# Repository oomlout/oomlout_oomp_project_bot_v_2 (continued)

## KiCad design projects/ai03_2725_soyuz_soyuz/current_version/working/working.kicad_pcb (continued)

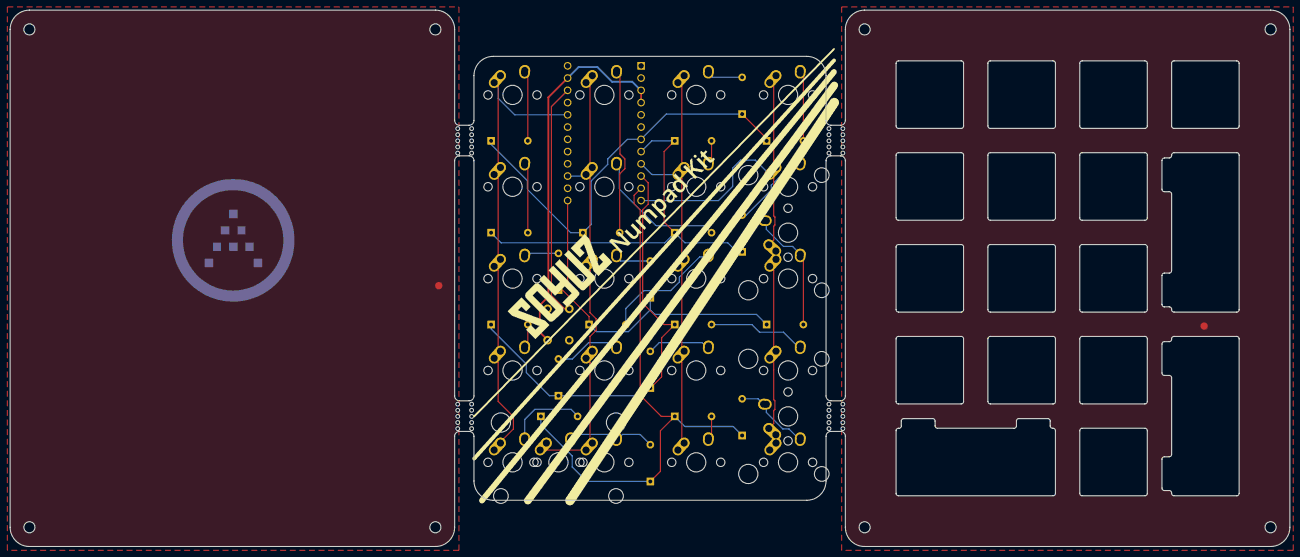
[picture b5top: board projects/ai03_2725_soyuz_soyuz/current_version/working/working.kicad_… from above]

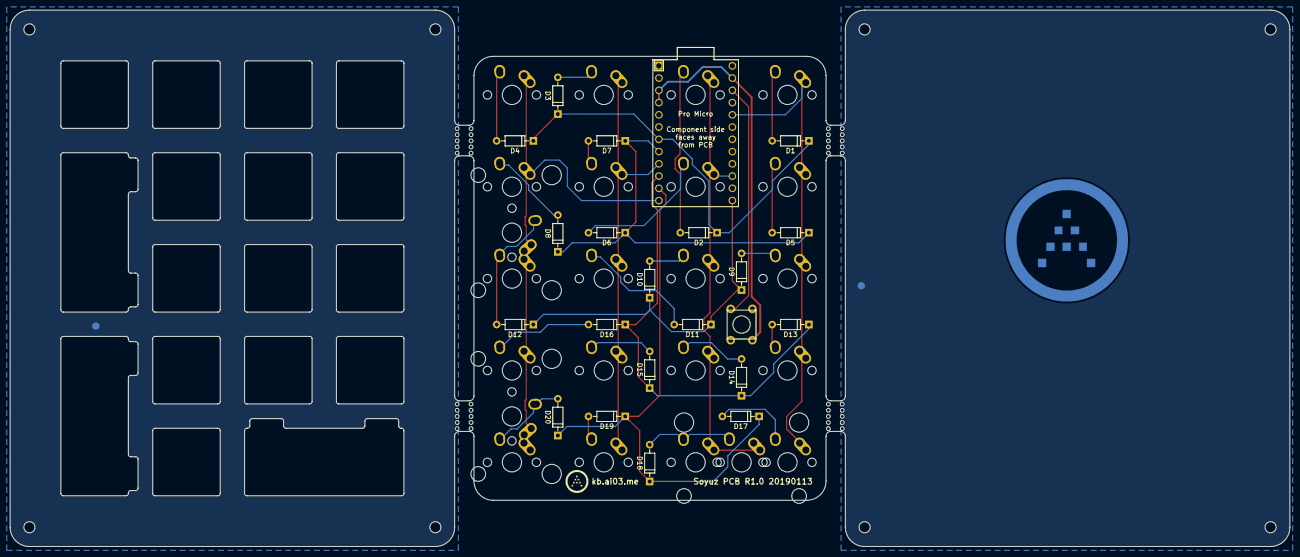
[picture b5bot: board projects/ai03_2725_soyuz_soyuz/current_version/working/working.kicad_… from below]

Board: 2 copper layers, 265.4 x 111.2 mm, 54 parts (22 on the bottom side), 31 nets.

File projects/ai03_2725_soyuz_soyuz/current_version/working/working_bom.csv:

"Id";"Designator";"Footprint";"Quantity";"Designation";"Supplier and ref";
1;"G***";"soyuz-logo-30mm";1;"LOGO";;;
2;"MX1,MX2,MX3,MX4,MX5,MX6,MX7,MX8,MX10,MX11,MX12,MX13,MX14,MX15,MX16,MX17,MX19,MX20,MX21,MX22";"MX-1U-NoLED";20;"MX-1U";;;
3;"MX9,MX18,MX23";"MX-2U-ReversedStabilizers-NoLED";3;"MX-2U";;;
4;"MOUSEBITE1,MOUSEBITE2,MOUSEBITE3,MOUSEBITE4,MOUSEBITE5,MOUSEBITE6,MOUSEBITE7,MOUSEBITE8";"breakaway-mousebites";8;"Mousebites";;;
5;"O1";"outline";1;"Outline";;;
6;"D1,D2,D3,D4,D5,D7,D8,D9,D10,D11,D12,D13,D14,D15,D16,D17,D18,D19,D20,D6";"D_DO-35_SOD27_P7.62mm_Horizontal";20;"1N4148";;;
7;"U1";"ProMicro-EnforcedTop";1;"ProMicro";;;
8;"G***";"ai-4.8-silk";1;"LOGO";;;
9;"G***";"ai-ring-25mm-mask";1;"LOGO";;;
10;"SW1";"PushButton_6x6mm_TH_Pretty";1;"SW_Push";;;
11;"G***";"soyuz-by-ai03";1;"LOGO";;;

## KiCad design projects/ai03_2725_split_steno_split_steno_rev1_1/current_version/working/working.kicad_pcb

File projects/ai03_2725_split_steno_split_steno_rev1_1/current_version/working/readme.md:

# split_steno
 
## summary 
* id: ai03_2725_split_steno_split_steno_rev1_1
* user: ai03_2725
* name: split_steno
* board: split_steno_rev1_1
* repo: https://github.com/ai03-2725/split_steno
* src_file_repo_kicad_pcb: rev1.1/split_steno_rev1.1.kicad_pcb
* src_file_repo_kicad_pcb_link: https://github.com/ai03-2725/split_steno/tree/master/rev1.1/split_steno_rev1.1.kicad_pcb

* src_file_repo_sch: rev1.1/split_steno_rev1.1.sch
* src_file_repo_sch_link: https://github.com/ai03-2725/split_steno/tree/master/rev1.1/split_steno_rev1.1.sch
* full details link: https://github.com/oomlout/oomlout_oomp_project_bot_v_2/tree/main/projects/ai03_2725_split_steno_split_steno_rev1_1/current_version/working  

## schematic  
  
[schematic (pdf)](working_schematic.pdf) 

## pcb  

[board (pdf)](working.pdf)  

## working_bom
| Id | Designator | Footprint | Quantity | Designation | Supplier and ref |  | None | 
| --- | --- | --- | --- | --- | --- | --- | --- | 
| 1 | REF**,REF**,REF**,REF** | MountingHole_3.2mm_M3_Pad | 4 |  |  |  | [''] | 
| 2 | REF** | TRRS-PJ-320A | 1 | TRRS-PJ-320A |  |  | [''] | 
| 3 | G***,G*** | airi_icon-7.6 | 2 | LOGO |  |  | [''] | 
| 4 | K1,K2,K3,K5,K6,K7,K8,K11,K12,K13,K18 | Hybrid_PCB_100H_Dual_hole | 11 | KEYSW |  |  | [''] | 
| 5 | K4,K9,K10,K14,K15,K16,K17 | Hybrid_PCB_100H_Dual_hole-flip | 7 | KEYSW |  |  | [''] | 
| 6 | K19,K20 | Hybrid_PCB_200H-dual-nosilk | 2 | KEYSW |  |  | [''] | 
| 7 | G*** | calvin | 1 | LOGO |  |  | [''] | 
| 8 | G***,G*** | watterson | 2 | LOGO |  |  | [''] | 
| 9 | C1 | CP_Radial_D5.0mm_P2.00mm | 1 | 100 |  |  | [''] | 
| 10 | D1,D2,D3,D4,D5,D6,D7,D8,D9,D10,D11,D12,D13,D14,D15,D16,D17,D18 | Diode-dual | 18 | D |  |  | [''] | 
| 11 | G*** | hobbes | 1 | LOGO |  |  | [''] | 
| 12 | J1 | TRRS-PJ-320A | 1 | i2c |  |  | [''] | 
| 13 | J2 | Pin_Header_Straight_1x04_Pitch2.54mm | 1 | serial |  |  | [''] | 
| 14 | J3 | Pin_Header_Straight_1x03_Pitch2.54mm | 1 | rgb |  |  | [''] | 
| 15 | J4 | Pin_Header_Straight_2x03_Pitch2.54mm | 1 | icsp |  |  | [''] | 
| 16 | J5 | Pin_Header_Straight_1x02_Pitch2.54mm | 1 | raw |  |  | [''] | 
| 17 | J6 | Pin_Header_Straight_1x01_Pitch2.54mm | 1 | extra |  |  | [''] | 
| 18 | R1,R2 | Resistor-Hybrid | 2 | 4.7k |  |  | [''] | 
| 19 | R3 | Resistor-Hybrid | 1 | 470 |  |  | [''] | 
| 20 | SW1 | SW_Tactile_SPST_Angled_MJTP1117 | 1 | reset |  |  | [''] | 
| 21 | U1 | ArduinoProMicro | 1 | ProMicro |  |  | [''] | 

## bom_schematic
| Ref | Qnty | Value | Cmp name | Footprint | Description | Vendor | DNP | 
| --- | --- | --- | --- | --- | --- | --- | --- | 
| C1 | 1 | 100 | C | lib_fp:CP_Radial_D5.0mm_P2.00mm |  |  |  | 
| D1, D2, D3, D4, D5, D6, D7, D8, D9, D10, D11, D12, D13, D14, D15, D16, D17, D18 | 18 | D | D | lib_fp:Diode-dual |  |  |  | 
| J1 | 1 | i2c | Audio-Jack-4 | lib_fp:TRRS-PJ-320A |  |  |  | 
| J2 | 1 | serial | Conn_01x04 | lib_fp:Pin_Header_Straight_1x04_Pitch2.54mm |  |  |  | 
| J3 | 1 | rgb | Conn_01x03 | lib_fp:Pin_Header_Straight_1x03_Pitch2.54mm |  |  |  | 
| J4 | 1 | icsp | Conn_02x03_Odd_Even | lib_fp:Pin_Header_Straight_2x03_Pitch2.54mm |  |  |  | 
| J5 | 1 | raw | Conn_01x02 | lib_fp:Pin_Header_Straight_1x02_Pitch2.54mm |  |  |  | 
| J6 | 1 | extra | Conn_01x01 | lib_fp:Pin_Header_Straight_1x01_Pitch2.54mm |  |  |  | 
| K1, K2, K3, K5, K6, K7, K8, K11, K12, K13, K18 | 11 | KEYSW | KEYSW | lib_fp:Hybrid_PCB_100H_Dual_hole |  |  |  | 
| K4, K9, K10, K14, K15, K16, K17 | 7 | KEYSW | KEYSW | lib_fp:Hybrid_PCB_100H_Dual_hole-flip |  |  |  | 
| K19, K20 | 2 | KEYSW | KEYSW | lib_fp:Hybrid_PCB_200H-dual-nosilk |  |  |  | 
| R1, R2 | 2 | 4.7k | R | lib_fp:Resistor-Hybrid |  |  |  | 
| R3 | 1 | 470 | R | lib_fp:Resistor-Hybrid |  |  |  | 
| SW1 | 1 | reset | SW_Push | lib_fp:SW_Tactile_SPST_Angled_MJTP1117 |  |  |  | 
| U1 | 1 | ProMicro | ProMicro | lib_fp:ArduinoProMicro |  |  |  | 

## mounting_holes
| x | y | package | value | ref | size | 
| --- | --- | --- | --- | --- | --- | 
| 0.0 | 55.0 | MountingHole_3.2mm_M3_Pad | nan | REF** | m3 | 
| 81.6 | 55.0 | MountingHole_3.2mm_M3_Pad | nan | REF** | m3 | 
| 10.8 | 0.0 | MountingHole_3.2mm_M3_Pad | nan | REF** | m3 | 
| 67.8 | 0.0 | MountingHole_3.2mm_M3_Pad | nan | REF** | m3 |

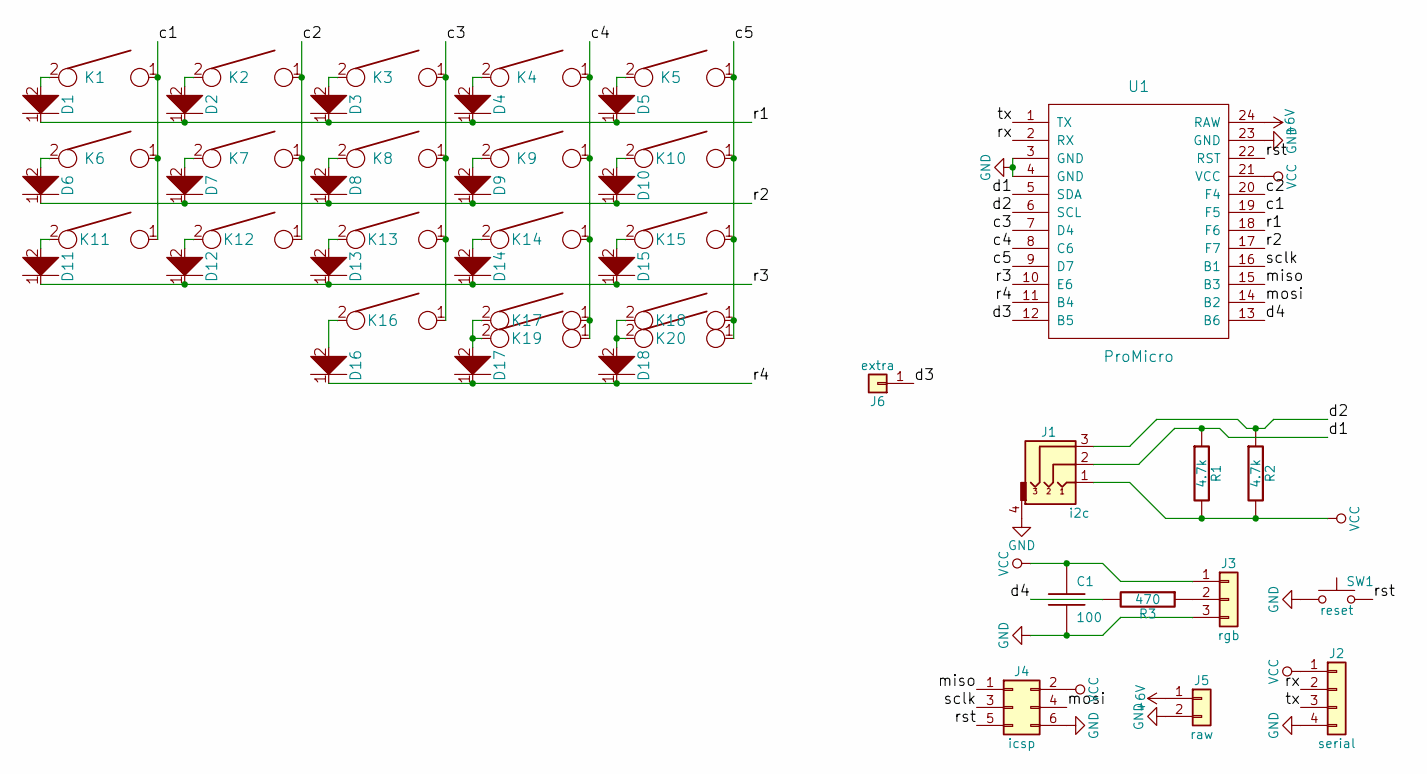
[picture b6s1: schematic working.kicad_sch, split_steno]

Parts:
C1: 100; CP_Radial_D5.0mm_P2.00mm
D1, D2, D3, D4, D5, D6, D7, D8, D9, D10, D11, D12, D13, D14, D15, D16, D17, D18: D; Diode-dual
J1: i2c; TRRS-PJ-320A
J2: serial; Pin_Header_Straight_1x04_Pitch2.54mm
J3: rgb; Pin_Header_Straight_1x03_Pitch2.54mm
J4: icsp; Pin_Header_Straight_2x03_Pitch2.54mm
J5: raw; Pin_Header_Straight_1x02_Pitch2.54mm
J6: extra; Pin_Header_Straight_1x01_Pitch2.54mm
K1, K2, K3, K5, K6, K7, K8, K11, K12, K13, K18: KEYSW; Hybrid_PCB_100H_Dual_hole
K4, K9, K10, K14, K15, K16, K17: KEYSW; Hybrid_PCB_100H_Dual_hole-flip
K19, K20: KEYSW; Hybrid_PCB_200H-dual-nosilk
R1, R2: 4.7k; Resistor-Hybrid
R3: 470; Resistor-Hybrid
SW1: reset; SW_Tactile_SPST_Angled_MJTP1117
U1: ProMicro; ArduinoProMicro

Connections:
+6V: J5.1, U1.24 (RAW)
/c1: K1.1, K6.1, K11.1, U1.19 (F5)
/c2: K2.1, K7.1, K12.1, U1.20 (F4)
/c3: K3.1, K8.1, K13.1, K16.1, U1.7 (D4)
/c4: K4.1, K9.1, K14.1, K17.1, K19.1, U1.8 (C6)
/c5: K5.1, K10.1, K15.1, K18.1, K20.1, U1.9 (D7)
/d1: J1.2, R1.1, U1.5 (SDA)
/d2: J1.3, R2.1, U1.6 (SCL)
/d3: J6.1, U1.12 (B5)
/d4: R3.2, U1.13 (B6)
/miso: J4.1, U1.15 (B3)
/mosi: J4.4, U1.14 (B2)
/r1: D1.1, D2.1, D3.1, D4.1, D5.1, U1.18 (F6)
/r2: D6.1, D7.1, D8.1, D9.1, D10.1, U1.17 (F7)
/r3: D11.1, D12.1, D13.1, D14.1, D15.1, U1.10 (E6)
/r4: D16.1, D17.1, D18.1, U1.11 (B4)
/rst: J4.5, SW1.2, U1.22 (RST)
/rx: J2.2, U1.2 (RX)
/sclk: J4.3, U1.16 (B1)
/tx: J2.3, U1.1 (TX)
GND: C1.2, J1.4, J2.4, J3.3, J4.6, J5.2, SW1.1, U1.3 (GND), U1.4 (GND), U1.23 (GND)
unnamed: D1.2, K1.2
unnamed: D2.2, K2.2
unnamed: D3.2, K3.2
unnamed: D4.2, K4.2
unnamed: D5.2, K5.2
unnamed: D6.2, K6.2
unnamed: D7.2, K7.2
unnamed: D8.2, K8.2
unnamed: D9.2, K9.2
unnamed: D10.2, K10.2
unnamed: D11.2, K11.2
unnamed: D12.2, K12.2
unnamed: D13.2, K13.2
unnamed: D14.2, K14.2
unnamed: D15.2, K15.2
unnamed: D16.2, K16.2
unnamed: D17.2, K17.2, K19.2
unnamed: D18.2, K18.2, K20.2
unnamed: J3.2, R3.1
VCC: C1.1, J1.1, J2.1, J3.1, J4.2, R1.2, R2.2, U1.21 (VCC)

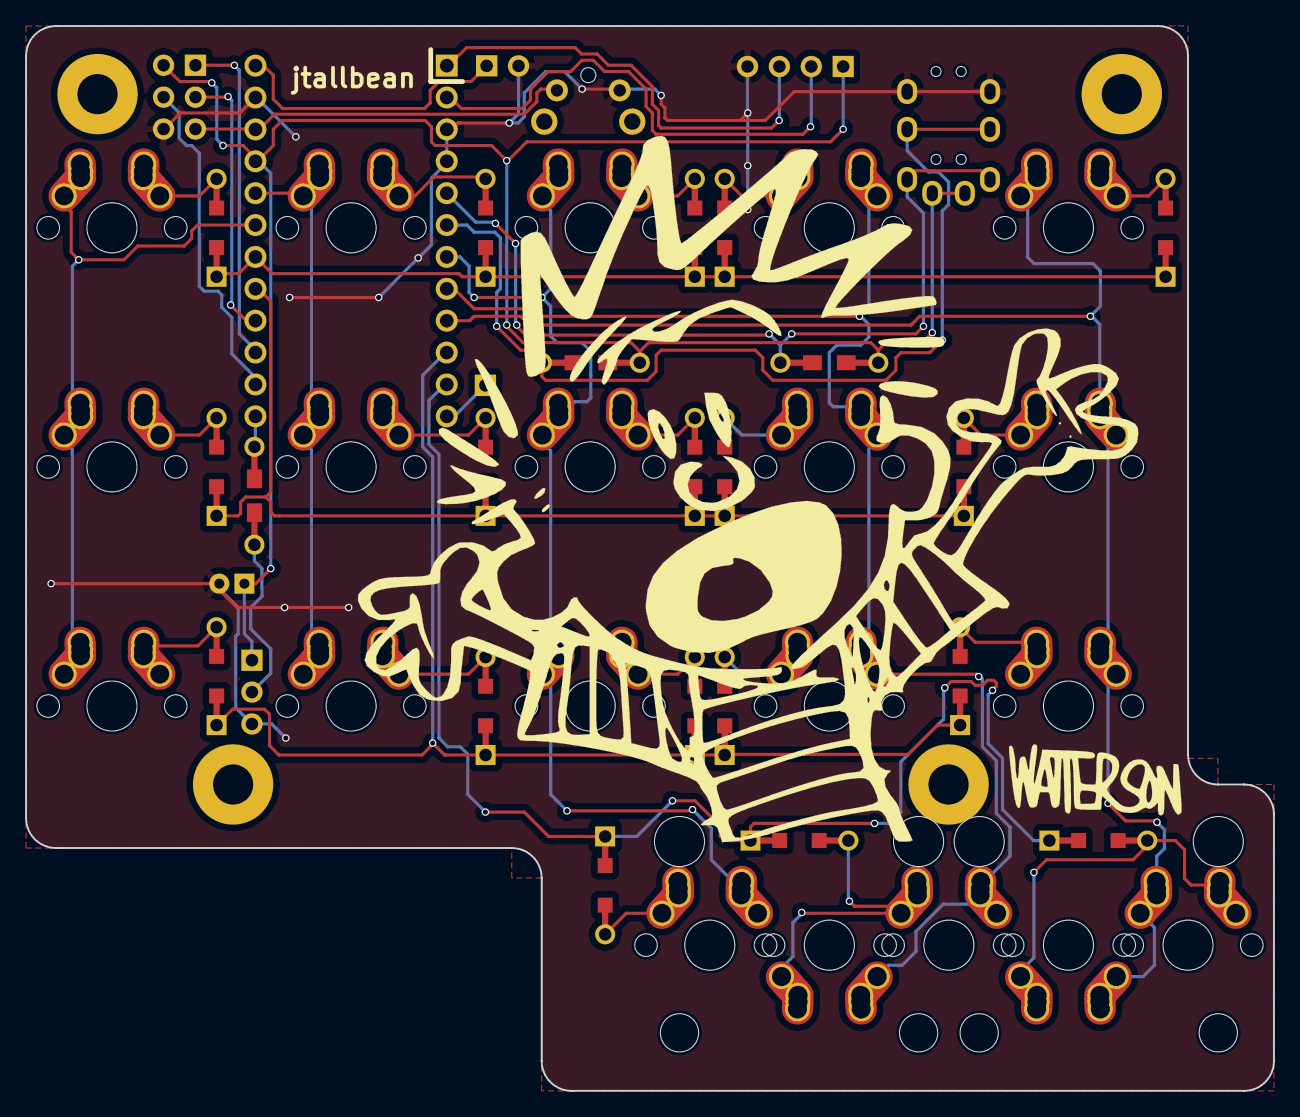
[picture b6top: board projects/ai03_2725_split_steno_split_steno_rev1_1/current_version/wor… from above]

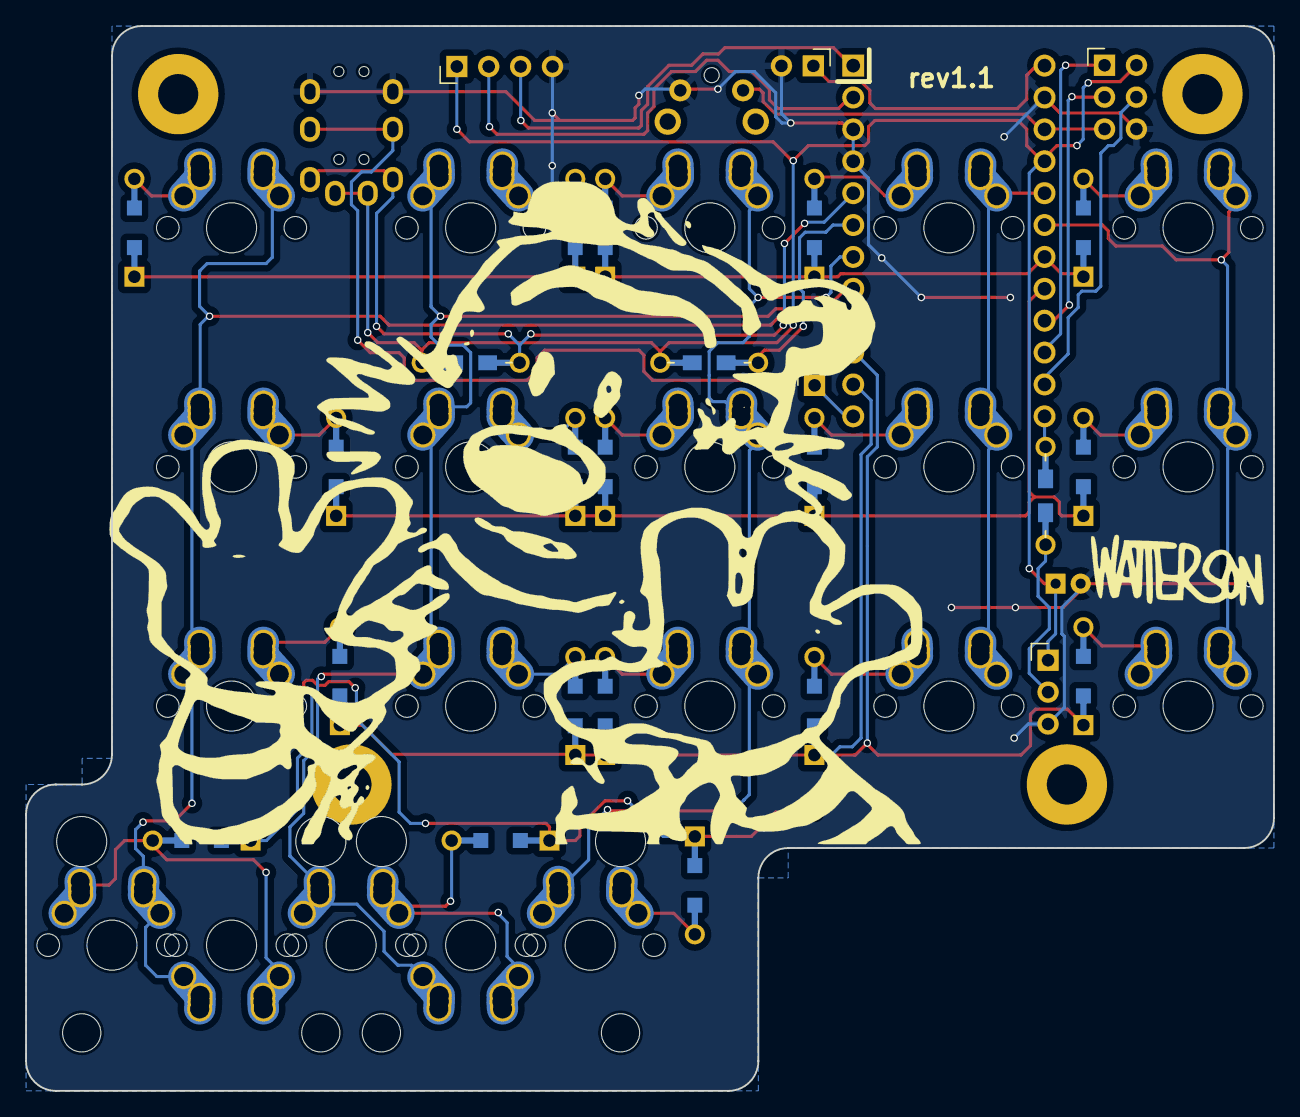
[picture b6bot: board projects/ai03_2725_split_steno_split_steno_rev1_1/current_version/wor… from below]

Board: 2 copper layers, 99.4 x 84.8 mm, 50 parts (30 on the bottom side), 41 nets.

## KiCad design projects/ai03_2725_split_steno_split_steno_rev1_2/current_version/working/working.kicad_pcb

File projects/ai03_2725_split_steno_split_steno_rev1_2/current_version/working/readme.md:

# split_steno
 
## summary 
* id: ai03_2725_split_steno_split_steno_rev1_2
* user: ai03_2725
* name: split_steno
* board: split_steno_rev1_2
* repo: https://github.com/ai03-2725/split_steno
* src_file_repo_kicad_pcb: rev1.2/split_steno_rev1.2.kicad_pcb
* src_file_repo_kicad_pcb_link: https://github.com/ai03-2725/split_steno/tree/master/rev1.2/split_steno_rev1.2.kicad_pcb

* src_file_repo_sch: rev1.2/split_steno_rev1.2.sch
* src_file_repo_sch_link: https://github.com/ai03-2725/split_steno/tree/master/rev1.2/split_steno_rev1.2.sch
* full details link: https://github.com/oomlout/oomlout_oomp_project_bot_v_2/tree/main/projects/ai03_2725_split_steno_split_steno_rev1_2/current_version/working  

## schematic  
  
[schematic (pdf)](working_schematic.pdf) 

## pcb  

[board (pdf)](working.pdf)  

## working_bom
| Id | Designator | Footprint | Quantity | Designation | Supplier and ref |  | None | 
| --- | --- | --- | --- | --- | --- | --- | --- | 
| 1 | MX1,MX2,MX3,MX4,MX5,MX6,MX7,MX8,MX9,MX10,MX11,MX12,MX13,MX14,MX15,MX16,MX18,MX20 | Hybrid_PCB_100H_Dual_hole-LED | 18 | MX-1U |  |  | [''] | 
| 2 | MX17,MX19 | Hybrid_PCB_200H-dual-LED | 2 | MX-1U |  |  | [''] | 
| 3 | SW1 | SW_Tactile_SPST_Angled_MJTP1117 | 1 | reset |  |  | [''] | 
| 4 | REF**,J1 | TRRS-PJ-320A | 2 | i2c |  |  | [''] | 
| 5 | REF**,REF**,REF**,REF** | MountingHole_3.2mm_M3_Pad | 4 |  |  |  | [''] | 
| 6 | G***,G*** | airi_icon-7.6 | 2 | LOGO |  |  | [''] | 
| 7 | C1 | CP_Radial_D5.0mm_P2.00mm | 1 | 100 |  |  | [''] | 
| 8 | D1,D2,D3,D4,D5,D6,D7,D8,D9,D10,D11,D12,D13,D14,D15,D16,D17,D18 | Diode-dual | 18 | D |  |  | [''] | 
| 9 | J2 | Pin_Header_Straight_1x04_Pitch2.54mm | 1 | serial |  |  | [''] | 
| 10 | J3 | Pin_Header_Straight_1x03_Pitch2.54mm | 1 | rgb |  |  | [''] | 
| 11 | J4 | Pin_Header_Straight_2x03_Pitch2.54mm | 1 | icsp |  |  | [''] | 
| 12 | J5 | Pin_Header_Straight_1x02_Pitch2.54mm | 1 | raw |  |  | [''] | 
| 13 | J6 | Pin_Header_Straight_1x01_Pitch2.54mm | 1 | extra |  |  | [''] | 
| 14 | Q1 | TO-92_Inline_Narrow_Oval | 1 | BC547 |  |  | [''] | 
| 15 | R1,R2,R3,R4,R5,R6,R7,R8,R9,R10,R11,R12,R13,R14,R15,R16,R17,R18 | Resistor-Hybrid | 18 | 51 |  |  | [''] | 
| 16 | R19 | Resistor-Hybrid | 1 | 470 |  |  | [''] | 
| 17 | R20 | Resistor-Hybrid | 1 | 1k |  |  | [''] | 
| 18 | R21,R22 | Resistor-Hybrid | 2 | 4.7k |  |  | [''] | 
| 19 | U1 | ArduinoProMicro | 1 | ProMicro |  |  | [''] | 

## bom_schematic
| Ref | Qnty | Value | Cmp name | Footprint | Description | Vendor | DNP | 
| --- | --- | --- | --- | --- | --- | --- | --- | 
| C1 | 1 | 100 | C | Capacitors_THT:CP_Radial_D5.0mm_P2.00mm |  |  |  | 
| D1, D2, D3, D4, D5, D6, D7, D8, D9, D10, D11, D12, D13, D14, D15, D16, D17, D18 | 18 | D | D | Keebio-Parts:Diode-dual |  |  |  | 
| J1 | 1 | i2c | Audio-Jack-4 | Keebio-Parts:TRRS-PJ-320A |  |  |  | 
| J2 | 1 | serial | Conn_01x04 | Pin_Headers:Pin_Header_Straight_1x04_Pitch2.54mm |  |  |  | 
| J3 | 1 | rgb | Conn_01x03 | Pin_Headers:Pin_Header_Straight_1x03_Pitch2.54mm |  |  |  | 
| J4 | 1 | icsp | Conn_02x03_Odd_Even | Pin_Headers:Pin_Header_Straight_2x03_Pitch2.54mm |  |  |  | 
| J5 | 1 | raw | Conn_01x02 | Pin_Headers:Pin_Header_Straight_1x02_Pitch2.54mm |  |  |  | 
| J6 | 1 | extra | Conn_01x01 | Pin_Headers:Pin_Header_Straight_1x01_Pitch2.54mm |  |  |  | 
| MX1, MX2, MX3, MX4, MX5, MX6, MX7, MX8, MX9, MX10, MX11, MX12, MX13, MX14, MX15, MX16, MX18, MX20 | 18 | MX-1U | MX-1U | Keebio-Parts:Hybrid_PCB_100H_Dual_hole-LED |  |  |  | 
| MX17, MX19 | 2 | MX-1U | MX-1U | Keebio-Parts:Hybrid_PCB_200H-dual-LED |  |  |  | 
| Q1 | 1 | BC547 | BC547 | TO_SOT_Packages_THT:TO-92_Inline_Narrow_Oval |  |  |  | 
| R1, R2, R3, R4, R5, R6, R7, R8, R9, R10, R11, R12, R13, R14, R15, R16, R17, R18 | 18 | 51 | R | Keebio-Parts:Resistor-Hybrid |  |  |  | 
| R19 | 1 | 470 | R | Keebio-Parts:Resistor-Hybrid |  |  |  | 
| R20 | 1 | 1k | R | Keebio-Parts:Resistor-Hybrid |  |  |  | 
| R21, R22 | 2 | 4.7k | R | Keebio-Parts:Resistor-Hybrid |  |  |  | 
| SW1 | 1 | reset | SW_Push | Keebio-Parts:SW_Tactile_SPST_Angled_MJTP1117 |  |  |  | 
| U1 | 1 | ProMicro | ProMicro | Keebio-Parts:ArduinoProMicro |  |  |  | 

## mounting_holes
| x | y | package | value | ref | size | 
| --- | --- | --- | --- | --- | --- | 
| 0.0 | 55.07 | MountingHole_3.2mm_M3_Pad | nan | REF** | m3 | 
| 82.45 | 55.07 | MountingHole_3.2mm_M3_Pad | nan | REF** | m3 | 
| 68.46 | 0.0 | MountingHole_3.2mm_M3_Pad | nan | REF** | m3 | 
| 11.31 | 0.0 | MountingHole_3.2mm_M3_Pad | nan | REF** | m3 |

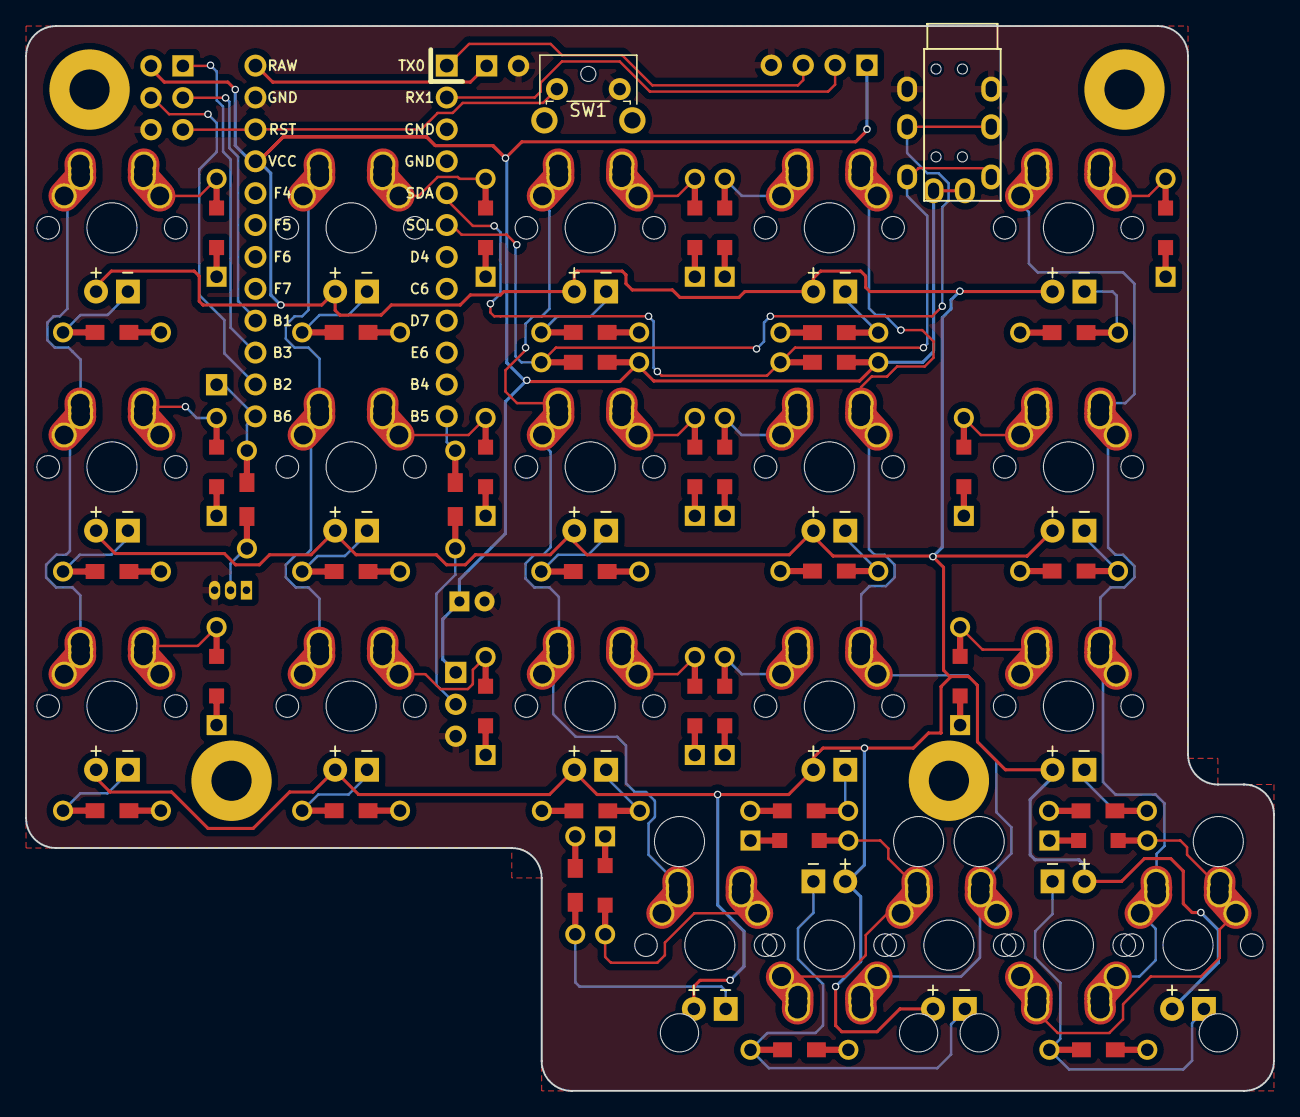
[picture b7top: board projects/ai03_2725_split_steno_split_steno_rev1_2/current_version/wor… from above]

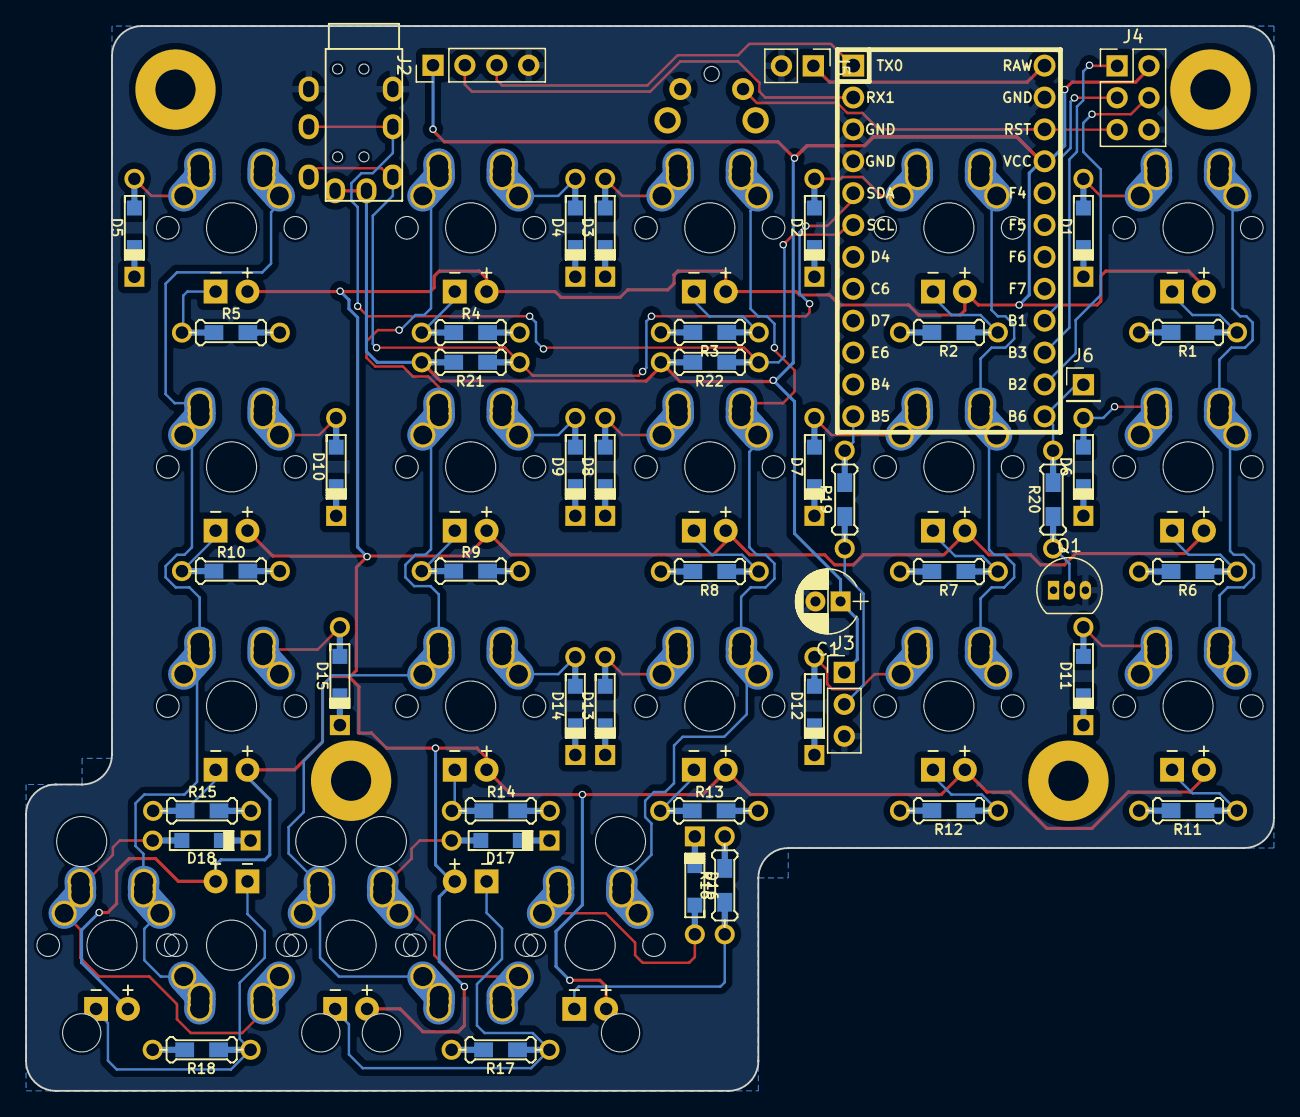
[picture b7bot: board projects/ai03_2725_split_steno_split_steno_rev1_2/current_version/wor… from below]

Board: 2 copper layers, 99.4 x 84.8 mm, 70 parts (49 on the bottom side), 61 nets.

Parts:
C1: 100; CP_Radial_D5.0mm_P2.00mm
D1, D2, D3, D4, D5, D6, D7, D8, D9, D10, D11, D12, D13, D14, D15, D16, D17, D18: D; Diode-dual
J1: i2c; TRRS-PJ-320A
J2: serial; Pin_Header_Straight_1x04_Pitch2.54mm
J3: rgb; Pin_Header_Straight_1x03_Pitch2.54mm
J4: icsp; Pin_Header_Straight_2x03_Pitch2.54mm
J5: raw; Pin_Header_Straight_1x02_Pitch2.54mm
J6: extra; Pin_Header_Straight_1x01_Pitch2.54mm
MX1, MX2, MX3, MX4, MX5, MX6, MX7, MX8, MX9, MX10, MX11, MX12, MX13, MX14, MX15, MX16, MX18, MX20: MX-1U; Hybrid_PCB_100H_Dual_hole-LED
MX17, MX19: MX-1U; Hybrid_PCB_200H-dual-LED
Q1: BC547; TO-92_Inline_Narrow_Oval
R1, R2, R3, R4, R5, R6, R7, R8, R9, R10, R11, R12, R13, R14, R15, R16, R17, R18: 51; Resistor-Hybrid
R19: 470; Resistor-Hybrid
R20: 1k; Resistor-Hybrid
R21, R22: 4.7k; Resistor-Hybrid
SW1: reset; SW_Tactile_SPST_Angled_MJTP1117
U1: ProMicro; ArduinoProMicro

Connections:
+6V: J5.1, U1.24
/c1: MX1.1, MX6.1, MX11.1, U1.19
/c2: MX2.1, MX7.1, MX12.1, U1.20
/c3: MX3.1, MX8.1, MX13.1, MX16.1, U1.7
/c4: MX4.2, MX9.2, MX14.2, MX17.1, MX18.2, U1.8
/c5: MX5.1, MX10.2, MX15.2, MX19.1, MX20.1, U1.9
/d1: J1.2, R21.1, U1.5
/d2: J1.3, R22.1, U1.6
/d3: R19.2, U1.12
/d4: J6.1, R20.2, U1.13
/miso: J4.1, U1.15
/mosi: J4.4, U1.14
/r1: D1.1, D2.1, D3.1, D4.1, D5.1, U1.18
/r2: D6.1, D7.1, D8.1, D9.1, D10.1, U1.17
/r3: D11.1, D12.1, D13.1, D14.1, D15.1, U1.10
/r4: D16.1, D17.1, D18.1, U1.11
/rst: J4.5, SW1.1, U1.22
/rx: J2.2, U1.2
/sclk: J4.3, U1.16
/tx: J2.3, U1.1
GND: C1.2, J1.4, J2.4, J3.3, J4.6, J5.2, Q1.3, SW1.2, U1.3, U1.4, U1.23
unnamed: D1.2, MX1.2
unnamed: D2.2, MX2.2
unnamed: D3.2, MX3.2
unnamed: D4.2, MX4.1
unnamed: D5.2, MX5.2
unnamed: D6.2, MX6.2
unnamed: D7.2, MX7.2
unnamed: D8.2, MX8.2
unnamed: D9.2, MX9.1
unnamed: D10.2, MX10.1
unnamed: D11.2, MX11.2
unnamed: D12.2, MX12.2
unnamed: D13.2, MX13.2
unnamed: D14.2, MX14.1
unnamed: D15.2, MX15.1
unnamed: D16.2, MX16.2
unnamed: D17.2, MX17.2, MX18.1
unnamed: D18.2, MX19.2, MX20.2
unnamed: J3.2, R19.1
unnamed: MX1.4, R1.1
unnamed: MX2.4, R2.1
unnamed: MX3.4, R3.1
unnamed: MX4.4, R4.1
unnamed: MX5.4, R5.1
unnamed: MX6.4, R6.1
unnamed: MX7.4, R7.1
unnamed: MX8.4, R8.1
unnamed: MX9.4, R9.1
unnamed: MX10.4, R10.1
unnamed: MX11.4, R11.1
unnamed: MX12.4, R12.1
unnamed: MX13.4, R13.1
unnamed: MX14.4, R14.1
unnamed: MX15.4, R15.1
unnamed: MX16.4, R16.1
unnamed: MX17.4, MX18.4, R17.1
unnamed: MX19.4, MX20.4, R18.1
unnamed: Q1.1, R1.2, R2.2, R3.2, R4.2, R5.2, R6.2, R7.2, R8.2, R9.2, R10.2, R11.2, R12.2, R13.2, R14.2, R15.2, R16.2, R17.2, R18.2
unnamed: Q1.2, R20.1
VCC: C1.1, J1.1, J2.1, J3.1, J4.2, MX1.3, MX2.3, MX3.3, MX4.3, MX5.3, MX6.3, MX7.3, MX8.3, MX9.3, MX10.3, MX11.3, MX12.3, MX13.3, MX14.3, MX15.3, MX16.3, MX17.3, MX18.3, MX19.3, MX20.3, R21.2, R22.2, U1.21
